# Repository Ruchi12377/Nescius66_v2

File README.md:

# Nescius66

## 画像ギャラリー

```bash
ergogen . && for i in output/cases/*.jscad; do npx @jscad/cli@1 "$i" -of stla; done
```

## Use external parts

add footprint to **/footprints** folder. then run command below

```bash
ergogen .
```

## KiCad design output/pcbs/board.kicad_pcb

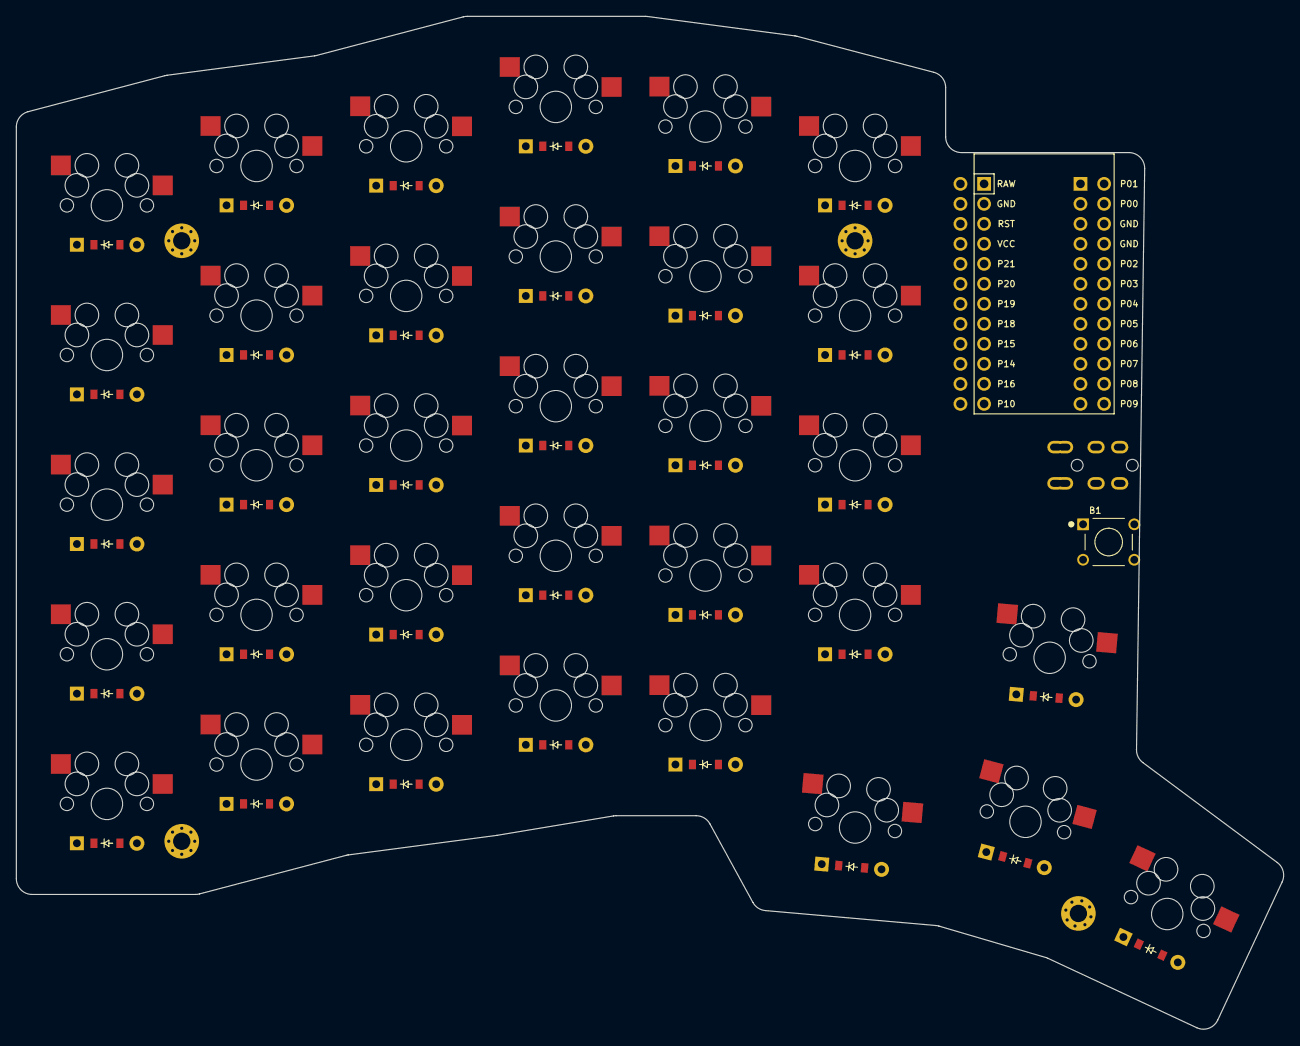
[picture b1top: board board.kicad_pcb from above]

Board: 2 copper layers, 160.9 x 128.6 mm, 74 parts (1 on the bottom side), 55 nets, no tracks yet.

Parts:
B1: SW_FSM8JH
D1, D2, D3, D4, D5, D6, D7, D8, D9, D10, D11, D12, D13, D14, D15, D16, D17, D18, D19, D20, D21, D22, D23, D24, D25, D26, D27, D28, D29, D30, D31, D32, D33: ComboDiode
MCU1, MCU2: ProMicro
S1, S2, S3, S4, S5, S6, S7, S8, S9, S10, S11, S12, S13, S14, S15, S16, S17, S18, S19, S20, S21, S22, S23, S24, S25, S26, S27, S28, S29, S30, S31, S32, S33: MX
TRRS1: TRRS-PJ-320A-dual
_1, _2, _3, _4: MountingHole_2.2mm_M2_Pad_Via

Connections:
GND: B1.2, MCU1.2, MCU1.15, MCU1.16, MCU2.2, MCU2.15, MCU2.16, TRRS1.1, TRRS1.2
P0: MCU1.14, MCU2.14
P1: MCU1.13, MCU2.13
P2: MCU1.17, MCU2.17, TRRS1.3
P3: MCU1.18, MCU2.18
P4: MCU1.19, MCU2.19
P5: MCU1.20, MCU2.20
P6: MCU1.21, MCU2.21, S16.1, S17.1, S18.1, S19.1, S20.1
P7: MCU1.22, MCU2.22, S21.1, S22.1, S23.1, S24.1, S25.1
P8: MCU1.23, MCU2.23, S26.1, S27.1, S28.1, S29.1, S31.1
P9: MCU1.24, MCU2.24, S30.1, S32.1, S33.1
P10: MCU1.12, MCU2.12, S11.1, S12.1, S13.1, S14.1, S15.1
P14: MCU1.10, MCU2.10, S1.1, S2.1, S3.1, S4.1, S5.1
P15: D1.1, D6.1, D11.1, D16.1, D21.1, D31.1, D32.1, D33.1, MCU1.9, MCU2.9
P16: MCU1.11, MCU2.11, S6.1, S7.1, S8.1, S9.1, S10.1
P18: D2.1, D7.1, D12.1, D17.1, D22.1, D26.1, D30.1, MCU1.8, MCU2.8
P19: D3.1, D8.1, D13.1, D18.1, D23.1, D27.1, MCU1.7, MCU2.7
P20: D4.1, D9.1, D14.1, D19.1, D24.1, D28.1, MCU1.6, MCU2.6
P21: D5.1, D10.1, D15.1, D20.1, D25.1, D29.1, MCU1.5, MCU2.5
RAW: MCU1.1, MCU2.1
RST: B1.1, MCU1.3, MCU2.3
VCC: MCU1.4, MCU2.4, TRRS1.4
base_cluster: D31.2, S31.2
bracket_bottom: D30.2, S30.2
index_bottom: D22.2, S22.2
index_home: D23.2, S23.2
index_mod: D21.2, S21.2
index_num: D25.2, S25.2
index_top: D24.2, S24.2
inner_bottom: D26.2, S26.2
inner_home: D27.2, S27.2
inner_num: D29.2, S29.2
inner_top: D28.2, S28.2
magic_cluster: D33.2, S33.2
middle_bottom: D17.2, S17.2
middle_home: D18.2, S18.2
middle_mod: D16.2, S16.2
middle_num: D20.2, S20.2
middle_top: D19.2, S19.2
outer_bottom: D2.2, S2.2
outer_home: D3.2, S3.2
outer_mod: D1.2, S1.2
outer_num: D5.2, S5.2
outer_top: D4.2, S4.2
pinky_bottom: D7.2, S7.2
pinky_home: D8.2, S8.2
pinky_mod: D6.2, S6.2
pinky_num: D10.2, S10.2
pinky_top: D9.2, S9.2
ring_bottom: D12.2, S12.2
ring_home: D13.2, S13.2
ring_mod: D11.2, S11.2
ring_num: D15.2, S15.2
ring_top: D14.2, S14.2
space_cluster: D32.2, S32.2

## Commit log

2024-11-17 init
2024-11-17 配線をした
2024-11-17 Revert "Update board.kicad_pcb"
    This reverts commit 021e51d17f41f71567862e83884dfb1eced45b6b.
2024-11-18 コマンドを追加
2024-11-21 ver1 完成
2024-11-23 ホットスワップようにフットプリントを修正
2024-11-23 不要なファイルを削除
2024-11-23 Create fp-info-cache
2024-11-23 ボタンをスルーホールに修正
2024-11-23 wrlを追加
2024-11-24 READMEに画像を追加
2024-11-27 トッププレートを追加
2024-12-04 ガーバーを追加
2024-12-04 不要なフォルダを削除
